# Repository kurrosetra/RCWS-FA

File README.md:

# RCWS-FA
RCWS TA2018 (First Article)

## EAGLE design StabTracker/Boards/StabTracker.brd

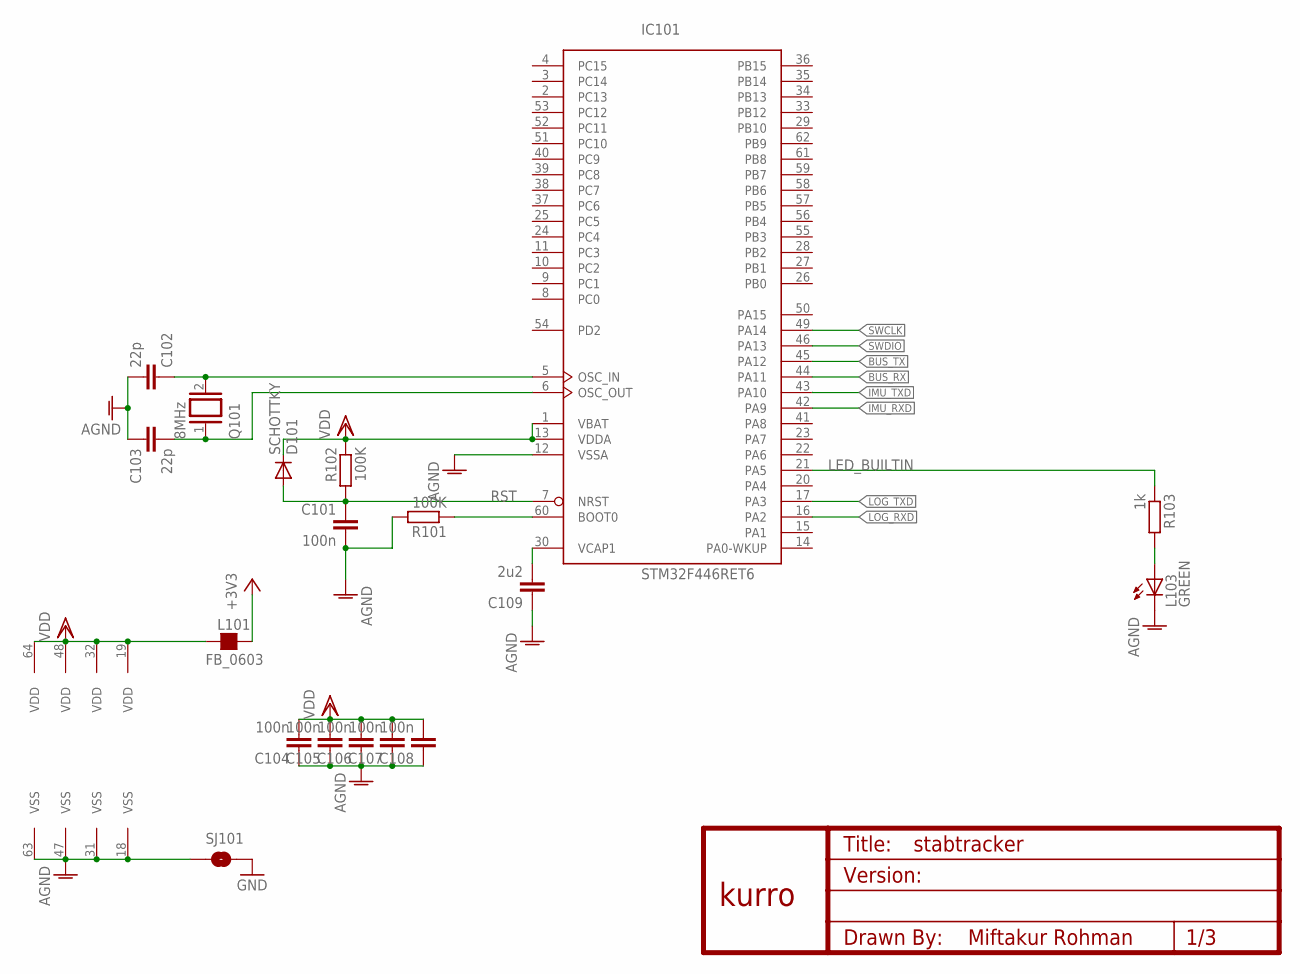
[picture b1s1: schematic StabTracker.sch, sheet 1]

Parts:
C101, C104, C105, C106, C107, C108: 100n; C0603
C102, C103: 22p; C0603
C109: 2u2; C0603
D101: SCHOTTKY; MICROMELF-W
IC101: STM32F446RET6; LQFP64
L101: FB_0603; L0603
L103: GREEN; CHIP-LED0805
Q101: 8MHz; QS
R101, R102: 100K; R0603
R103: 1k; R0603
SJ101: SOLDERJUMPERTRACE; SJ_2S-TRACE
U$1: KURRO_FOOTPRINT; KURRO-LOGO

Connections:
+3V3: L101.2; also elsewhere on the board
AGND: C101.2, C102.2, C103.1, C104.1, C105.1, C106.1, C107.1, C108.1, C109.1, IC101.12 (VSSA), IC101.18 (VSS), IC101.31 (VSS), IC101.47 (VSS), IC101.63 (VSS), L103.C, R101.2, SJ101.1; also elsewhere on the board
BOOT0: IC101.60 (BOOT0), R101.1
BUS_RX: IC101.44 (PA11); also elsewhere on the board
BUS_TX: IC101.45 (PA12); also elsewhere on the board
GND: SJ101.2; also elsewhere on the board
IMU_RXD: IC101.42 (PA9); also elsewhere on the board
IMU_TXD: IC101.43 (PA10); also elsewhere on the board
LED_BUILTIN: IC101.21 (PA5), R103.1
LOG_RXD: IC101.16 (PA2); also elsewhere on the board
LOG_TXD: IC101.17 (PA3); also elsewhere on the board
unnamed: C103.2, IC101.6 (OSC_OUT), Q101.1
unnamed: C102.1, IC101.5 (OSC_IN), Q101.2
unnamed: C109.2, IC101.30 (VCAP1)
unnamed: L103.A, R103.2
RST: C101.1, D101.A, IC101.7 (NRST), R102.2
SWCLK: IC101.49 (PA14); also elsewhere on the board
SWDIO: IC101.46 (PA13); also elsewhere on the board
VDD: C104.2, C105.2, C106.2, C107.2, C108.2, D101.C, IC101.1 (VBAT), IC101.13 (VDDA), IC101.19 (VDD), IC101.32 (VDD), IC101.48 (VDD), IC101.64 (VDD), L101.1, R102.1

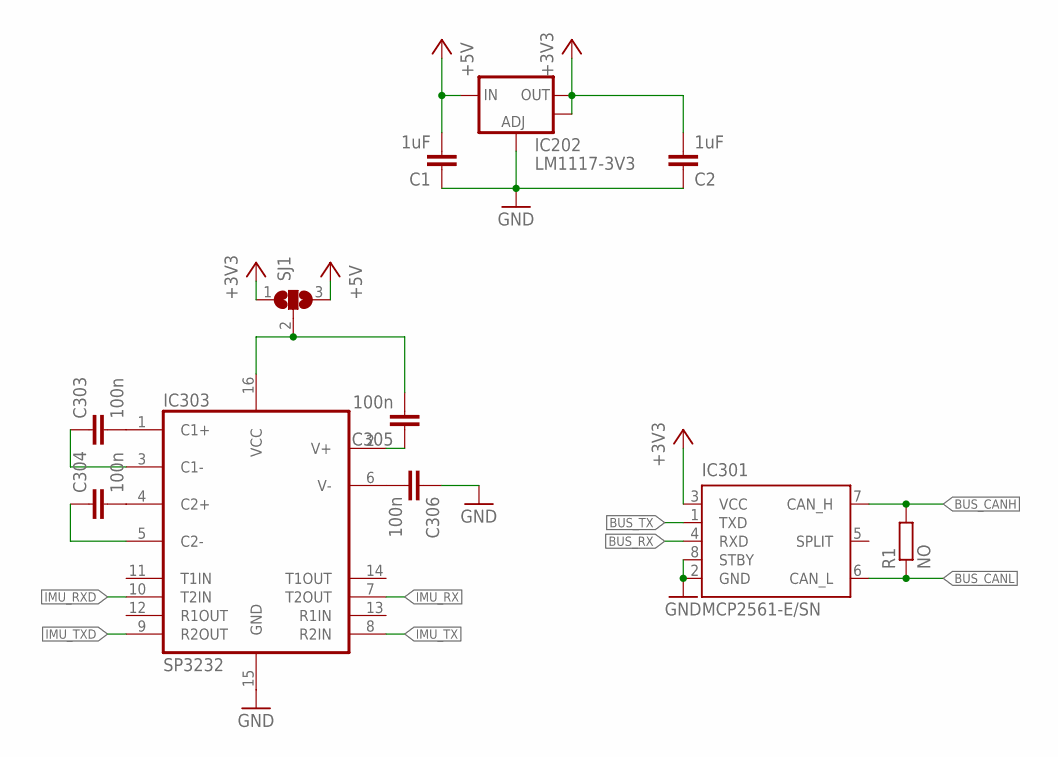
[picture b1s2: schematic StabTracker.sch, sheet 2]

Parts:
C1, C2: 1uF; C0603
C303, C304, C305, C306: 100n; C0603
IC202: LM1117-3V3; SOT223
IC301: MCP2561-E/SN; SOIC-8
IC303: SP3232; SO016
R1: NO; R0603
SJ1: SJ2W-TRACE; SJ2

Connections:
+3V3: C2.2, IC202.2 (OUT), IC202.4 (OUT), IC301.3 (VCC), SJ1.1; also elsewhere on the board
+5V: C1.2, IC202.3 (IN), SJ1.3; also elsewhere on the board
BUS_CANH: IC301.7 (CAN_H), R1.2; also elsewhere on the board
BUS_CANL: IC301.6 (CAN_L), R1.1; also elsewhere on the board
BUS_RX: IC301.4 (RXD); also elsewhere on the board
BUS_TX: IC301.1 (TXD); also elsewhere on the board
GND: C1.1, C2.1, C306.1, IC202.1 (ADJ), IC301.2 (GND), IC301.8 (STBY), IC303.15 (GND); also elsewhere on the board
IMU_RX: IC303.7 (T2OUT); also elsewhere on the board
IMU_RXD: IC303.10 (T2IN); also elsewhere on the board
IMU_TX: IC303.8 (R2IN); also elsewhere on the board
IMU_TXD: IC303.9 (R2OUT); also elsewhere on the board
unnamed: C305.2, IC303.16 (VCC), SJ1.2
unnamed: C306.2, IC303.6 (V-)
unnamed: C303.2, IC303.1 (C1+)
unnamed: C304.2, IC303.4 (C2+)
unnamed: C303.1, IC303.3 (C1-)
unnamed: C304.1, IC303.5 (C2-)
unnamed: C305.1, IC303.2 (V+)

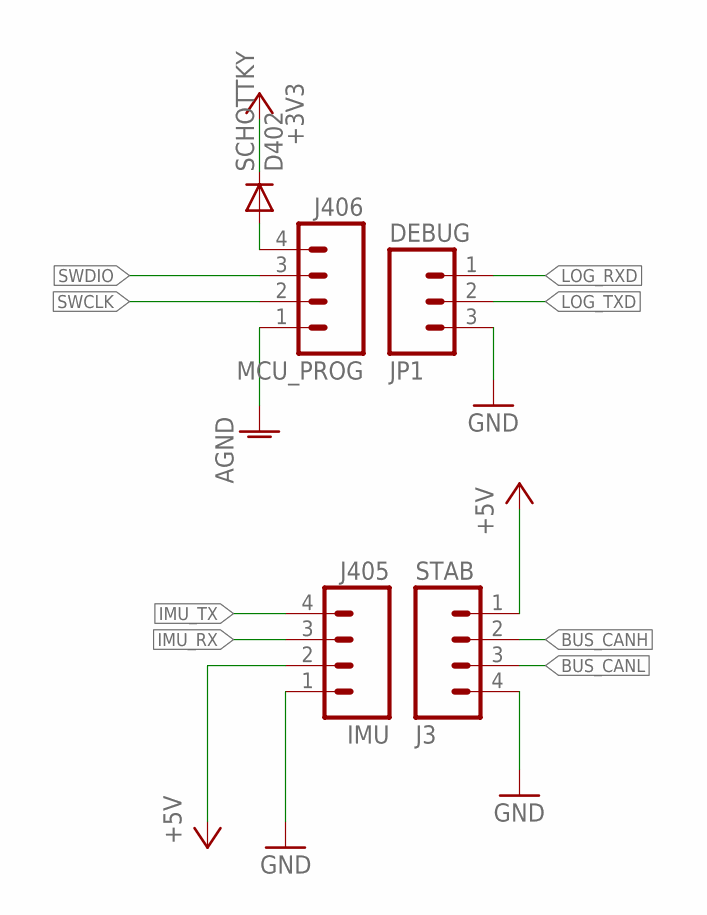
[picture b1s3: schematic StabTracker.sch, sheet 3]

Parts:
D402: SCHOTTKY; MICROMELF-W
J3: STAB; XH-4-RA
J405: IMU; XH-4-RA
J406: MCU_PROG; XH-4-RA
JP1: DEBUG; XH-3-RA

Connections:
+3V3: D402.C; also elsewhere on the board
+5V: J3.1, J405.2; also elsewhere on the board
AGND: J406.1; also elsewhere on the board
BUS_CANH: J3.2; also elsewhere on the board
BUS_CANL: J3.3; also elsewhere on the board
GND: J3.4, J405.1, JP1.3; also elsewhere on the board
IMU_RX: J405.3; also elsewhere on the board
IMU_TX: J405.4; also elsewhere on the board
LOG_RXD: JP1.1; also elsewhere on the board
LOG_TXD: JP1.2; also elsewhere on the board
unnamed: D402.A, J406.4
SWCLK: J406.2; also elsewhere on the board
SWDIO: J406.3; also elsewhere on the board

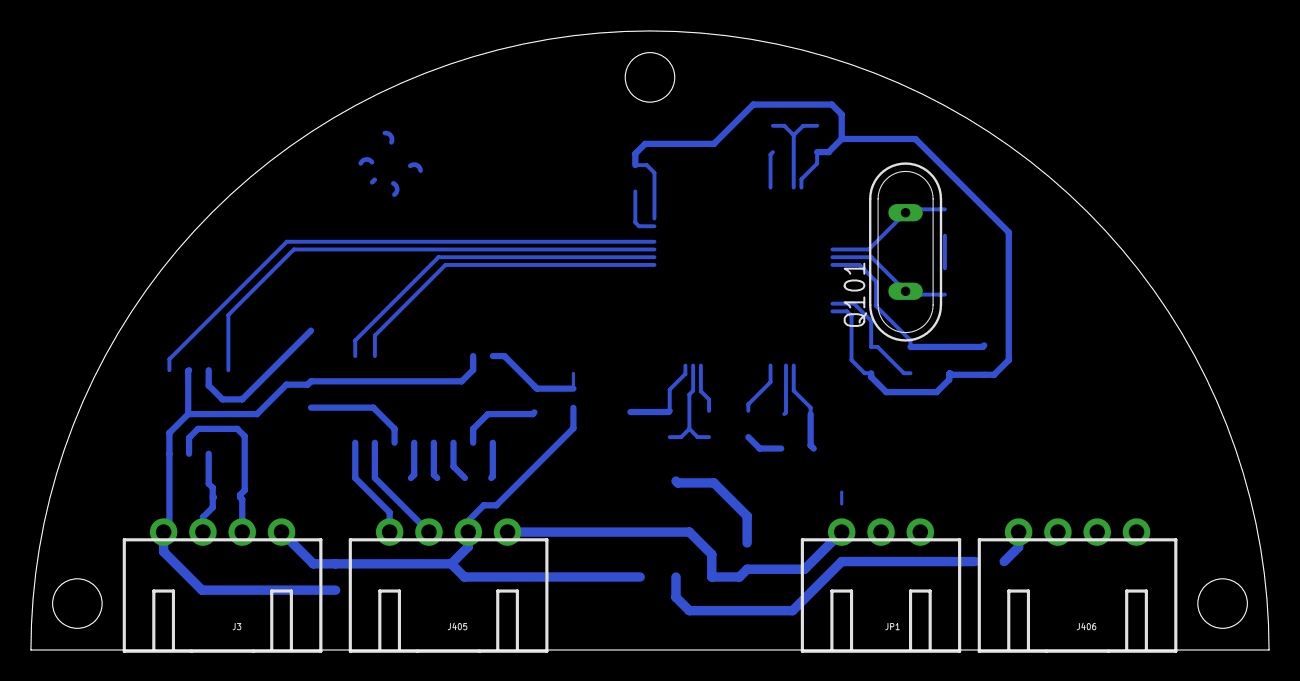
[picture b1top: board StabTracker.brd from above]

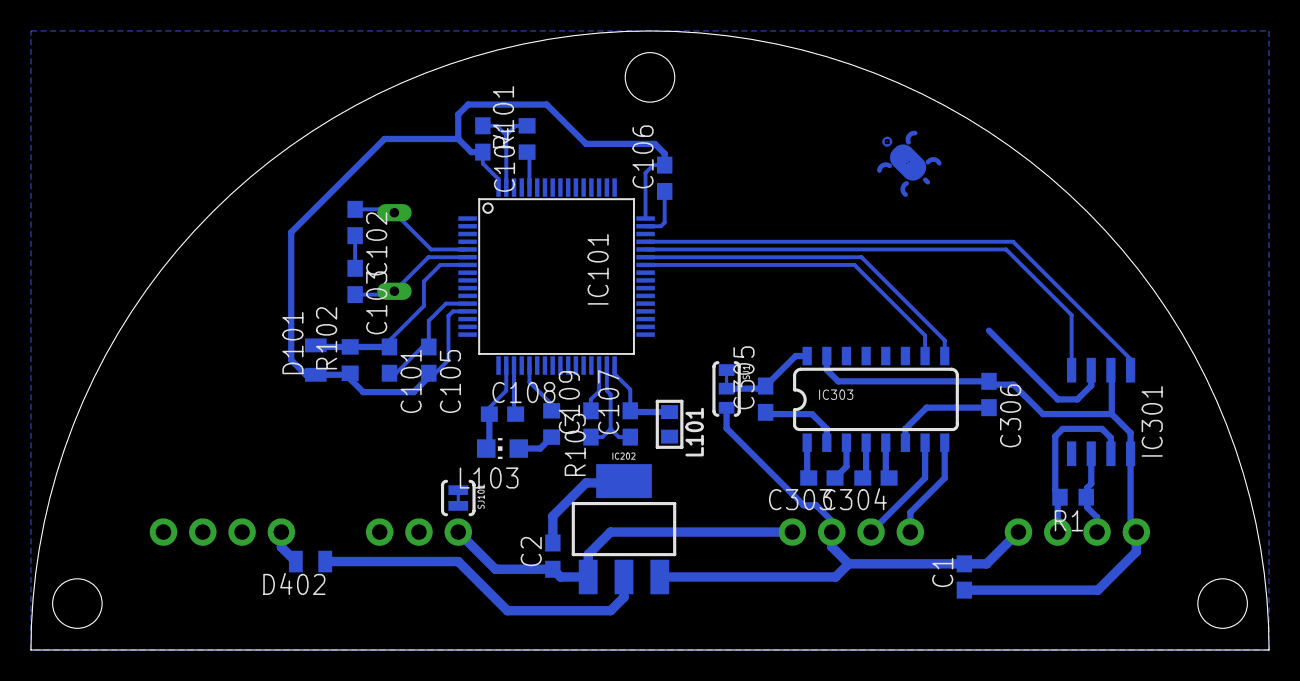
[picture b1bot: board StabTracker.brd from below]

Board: 2 copper layers, 80.0 x 40.0 mm, 35 parts (29 on the bottom side), 32 nets.

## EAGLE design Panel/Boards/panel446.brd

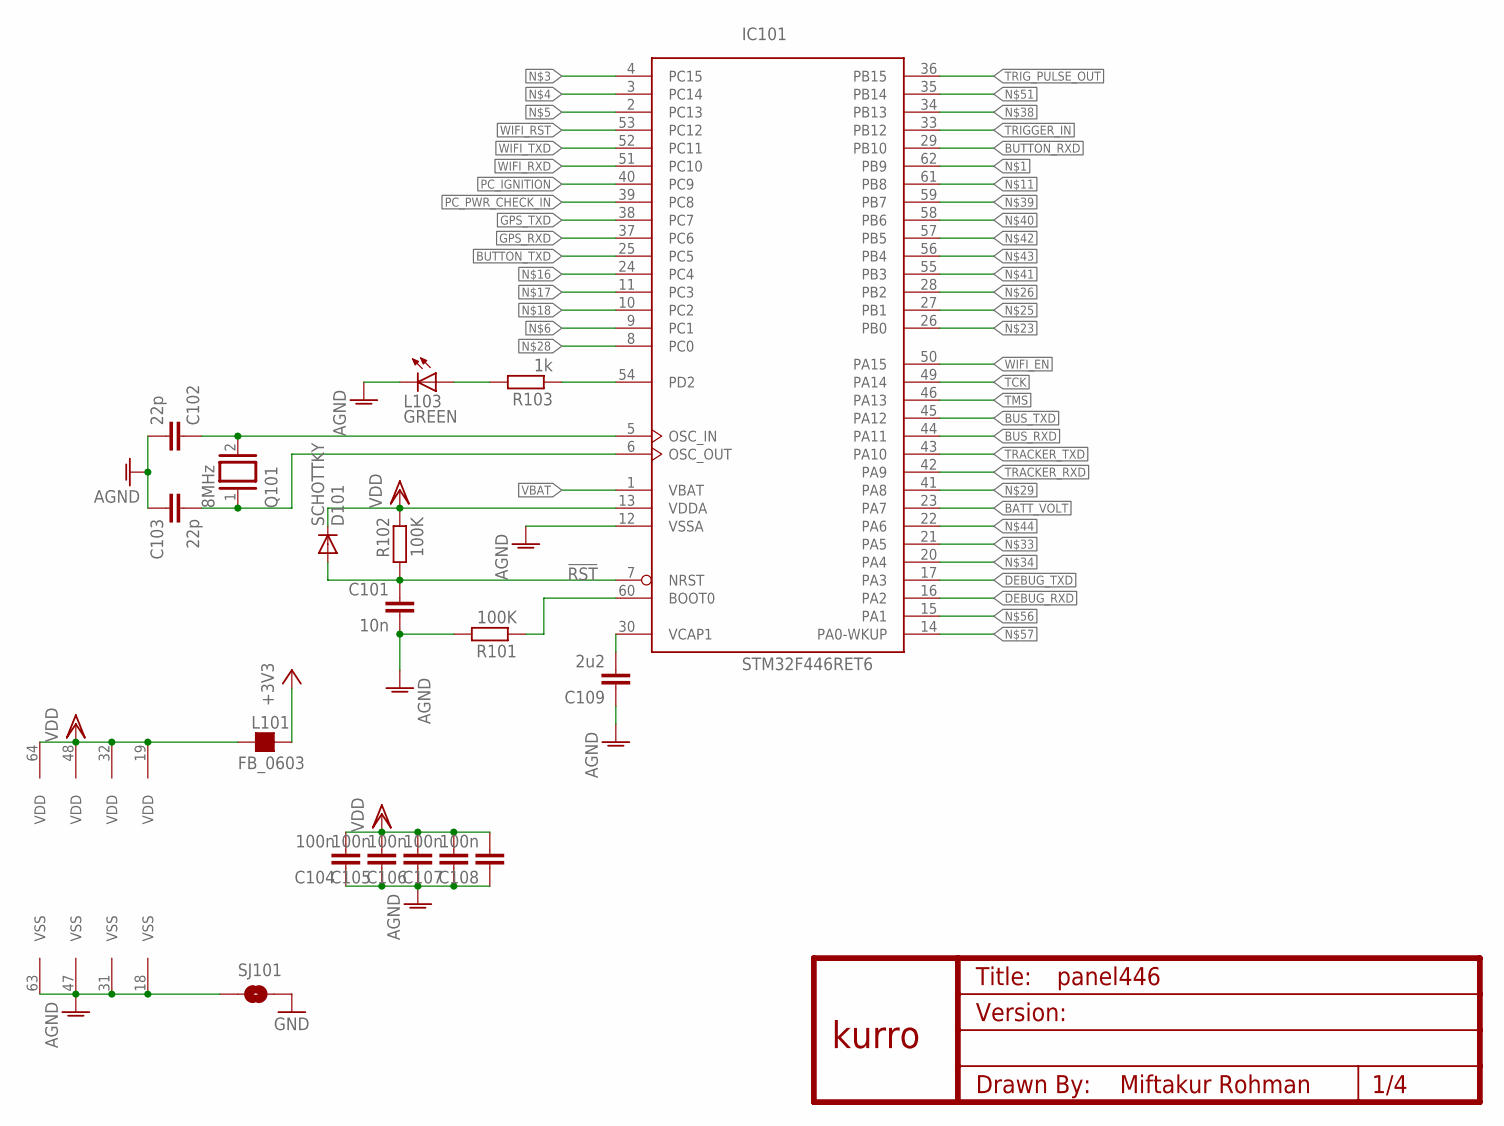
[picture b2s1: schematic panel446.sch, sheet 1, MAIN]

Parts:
C101: 10n; C0603
C102, C103: 22p; C0603
C104, C105, C106, C107, C108: 100n; C0603
C109: 2u2; C0805
D101: SCHOTTKY; MICROMELF-W
IC101: STM32F446RET6; LQFP64
L101: FB_0603; L0603
L103: GREEN; CHIP-LED0805
Q101: 8MHz; QS
R101, R102: 100K; R0603
R103: 1k; R0603
SJ101: SOLDERJUMPERTRACE; SJ_2S-TRACE
U$1: KURRO_FOOTPRINT; KURRO-LOGO

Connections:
!RST: C101.1, D101.A, IC101.7 (NRST), R102.2; also elsewhere on the board
+3V3: L101.2; also elsewhere on the board
AGND: C101.2, C102.2, C103.1, C104.1, C105.1, C106.1, C107.1, C108.1, C109.1, IC101.12 (VSSA), IC101.18 (VSS), IC101.31 (VSS), IC101.47 (VSS), IC101.63 (VSS), L103.C, R101.2, SJ101.1; also elsewhere on the board
BATT_VOLT: IC101.23 (PA7); also elsewhere on the board
BOOT1: IC101.60 (BOOT0), R101.1
BUS_RXD: IC101.44 (PA11); also elsewhere on the board
BUS_TXD: IC101.45 (PA12); also elsewhere on the board
BUTTON_RXD: IC101.29 (PB10); also elsewhere on the board
BUTTON_TXD: IC101.25 (PC5); also elsewhere on the board
DEBUG_RXD: IC101.16 (PA2); also elsewhere on the board
DEBUG_TXD: IC101.17 (PA3); also elsewhere on the board
GND: SJ101.2; also elsewhere on the board
GPS_RXD: IC101.37 (PC6); also elsewhere on the board
GPS_TXD: IC101.38 (PC7); also elsewhere on the board
unnamed: C109.2, IC101.30 (VCAP1)
unnamed: IC101.54 (PD2), R103.1
unnamed: L103.A, R103.2
unnamed: C103.2, IC101.6 (OSC_OUT), Q101.1
unnamed: C102.1, IC101.5 (OSC_IN), Q101.2
PC_IGNITION: IC101.40 (PC9); also elsewhere on the board
PC_PWR_CHECK_IN: IC101.39 (PC8); also elsewhere on the board
TCK: IC101.49 (PA14); also elsewhere on the board
TMS: IC101.46 (PA13); also elsewhere on the board
TRACKER_RXD: IC101.42 (PA9); also elsewhere on the board
TRACKER_TXD: IC101.43 (PA10); also elsewhere on the board
TRIGGER_IN: IC101.33 (PB12); also elsewhere on the board
TRIG_PULSE_OUT: IC101.36 (PB15); also elsewhere on the board
VBAT: IC101.1 (VBAT)
VDD: C104.2, C105.2, C106.2, C107.2, C108.2, D101.C, IC101.13 (VDDA), IC101.19 (VDD), IC101.32 (VDD), IC101.48 (VDD), IC101.64 (VDD), L101.1, R102.1; also elsewhere on the board
WIFI_EN: IC101.50 (PA15); also elsewhere on the board
WIFI_RST: IC101.53 (PC12); also elsewhere on the board
WIFI_RXD: IC101.51 (PC10); also elsewhere on the board
WIFI_TXD: IC101.52 (PC11); also elsewhere on the board

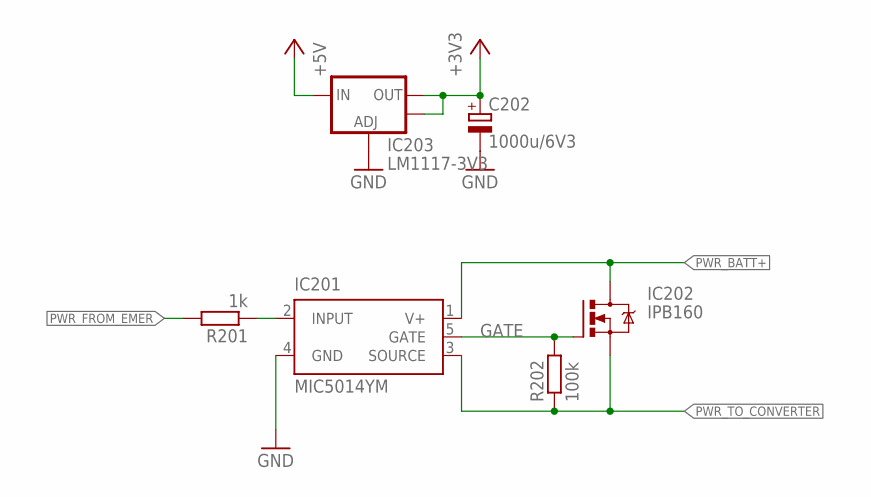
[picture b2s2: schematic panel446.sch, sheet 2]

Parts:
C202: 1000u/6V3; 153CLV-0810
IC201: MIC5014YM; SO-08
IC202: IPB160; PG-TO263-7
IC203: LM1117-3V3; SOT223
R201: 1k; R0603
R202: 100k; R0603

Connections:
+3V3: C202.+, IC203.2 (OUT), IC203.4 (OUT); also elsewhere on the board
+5V: IC203.3 (IN); also elsewhere on the board
GATE: IC201.5 (GATE), IC202.1 (G), R202.2
GND: C202.-, IC201.4 (GND), IC203.1 (ADJ); also elsewhere on the board
unnamed: IC201.2 (INPUT), R201.1
PWR_BATT+: IC201.1 (V+), IC202.4 (D); also elsewhere on the board
PWR_FROM_EMER: R201.2; also elsewhere on the board
PWR_TO_CONVERTER: IC201.3 (SOURCE), IC202.2 (S), IC202.3 (S), IC202.5 (S), IC202.6 (S), IC202.7 (S), R202.1; also elsewhere on the board

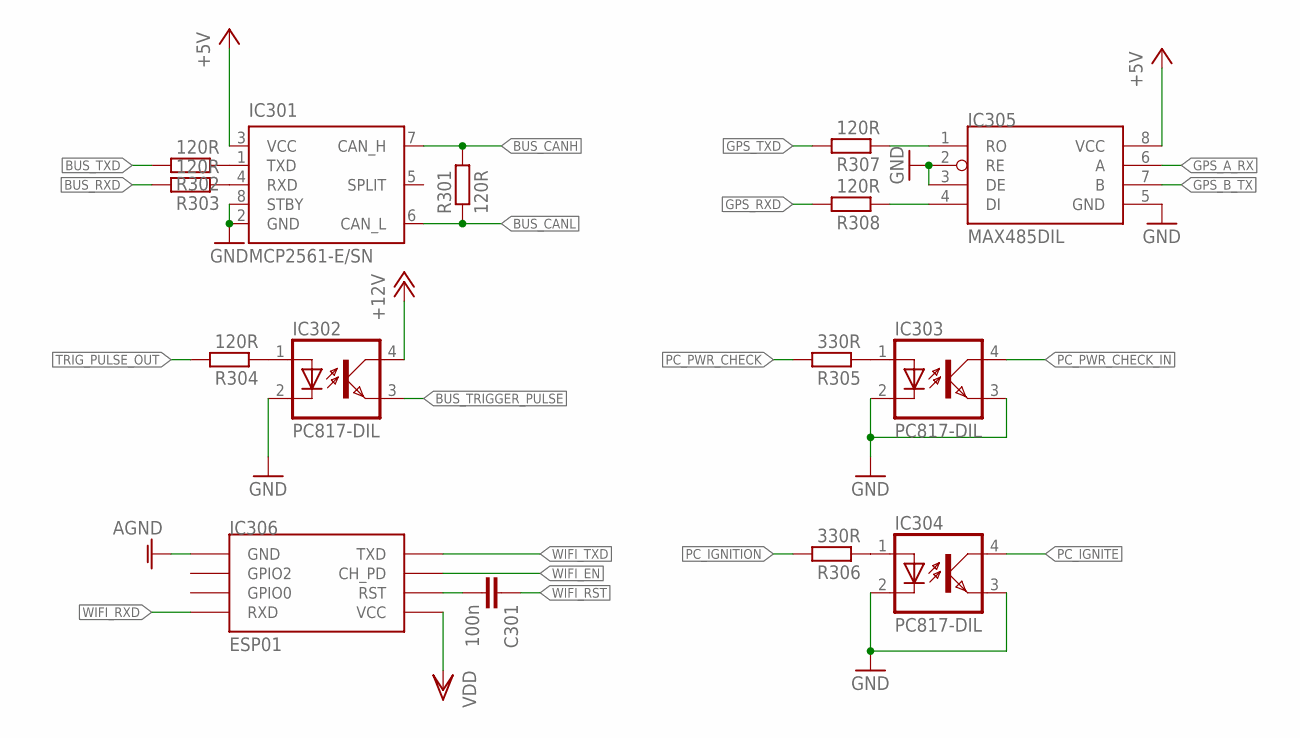
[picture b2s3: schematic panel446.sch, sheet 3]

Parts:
C301: 100n; C0603
IC301: MCP2561-E/SN; SOIC-8
IC302, IC303, IC304: PC817-DIL; DIL04A
IC305: MAX485DIL; DIL08
IC306: ESP01
R301, R302, R303, R304, R307, R308: 120R; R0603
R305, R306: 330R; R0603

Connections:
+5V: IC301.3 (VCC), IC305.8 (VCC); also elsewhere on the board
+12V: IC302.4 (COL); also elsewhere on the board
AGND: IC306.GND; also elsewhere on the board
BUS_CANH: IC301.7 (CAN_H), R301.2; also elsewhere on the board
BUS_CANL: IC301.6 (CAN_L), R301.1; also elsewhere on the board
BUS_RXD: R303.2; also elsewhere on the board
BUS_TRIGGER_PULSE: IC302.3 (EMIT); also elsewhere on the board
BUS_TXD: R302.2; also elsewhere on the board
GND: IC301.2 (GND), IC301.8 (STBY), IC302.2 (C), IC303.2 (C), IC303.3 (EMIT), IC304.2 (C), IC304.3 (EMIT), IC305.2 (RE), IC305.3 (DE), IC305.5 (GND); also elsewhere on the board
GPS_A_RX: IC305.6 (A); also elsewhere on the board
GPS_B_TX: IC305.7 (B); also elsewhere on the board
GPS_RXD: R308.2; also elsewhere on the board
GPS_TXD: R307.2; also elsewhere on the board
unnamed: C301.2, IC306.RST
unnamed: IC301.4 (RXD), R303.1
unnamed: IC301.1 (TXD), R302.1
unnamed: IC302.1 (A), R304.1
unnamed: IC303.1 (A), R305.1
unnamed: IC305.1 (RO), R307.1
unnamed: IC305.4 (DI), R308.1
unnamed: IC304.1 (A), R306.1
PC_IGNITE: IC304.4 (COL); also elsewhere on the board
PC_IGNITION: R306.2; also elsewhere on the board
PC_PWR_CHECK: R305.2; also elsewhere on the board
PC_PWR_CHECK_IN: IC303.4 (COL); also elsewhere on the board
TRIG_PULSE_OUT: R304.2; also elsewhere on the board
VDD: IC306.VCC; also elsewhere on the board
WIFI_EN: IC306.CH_PD; also elsewhere on the board
WIFI_RST: C301.1; also elsewhere on the board
WIFI_RXD: IC306.RX (RXD); also elsewhere on the board
WIFI_TXD: IC306.TX (TXD); also elsewhere on the board

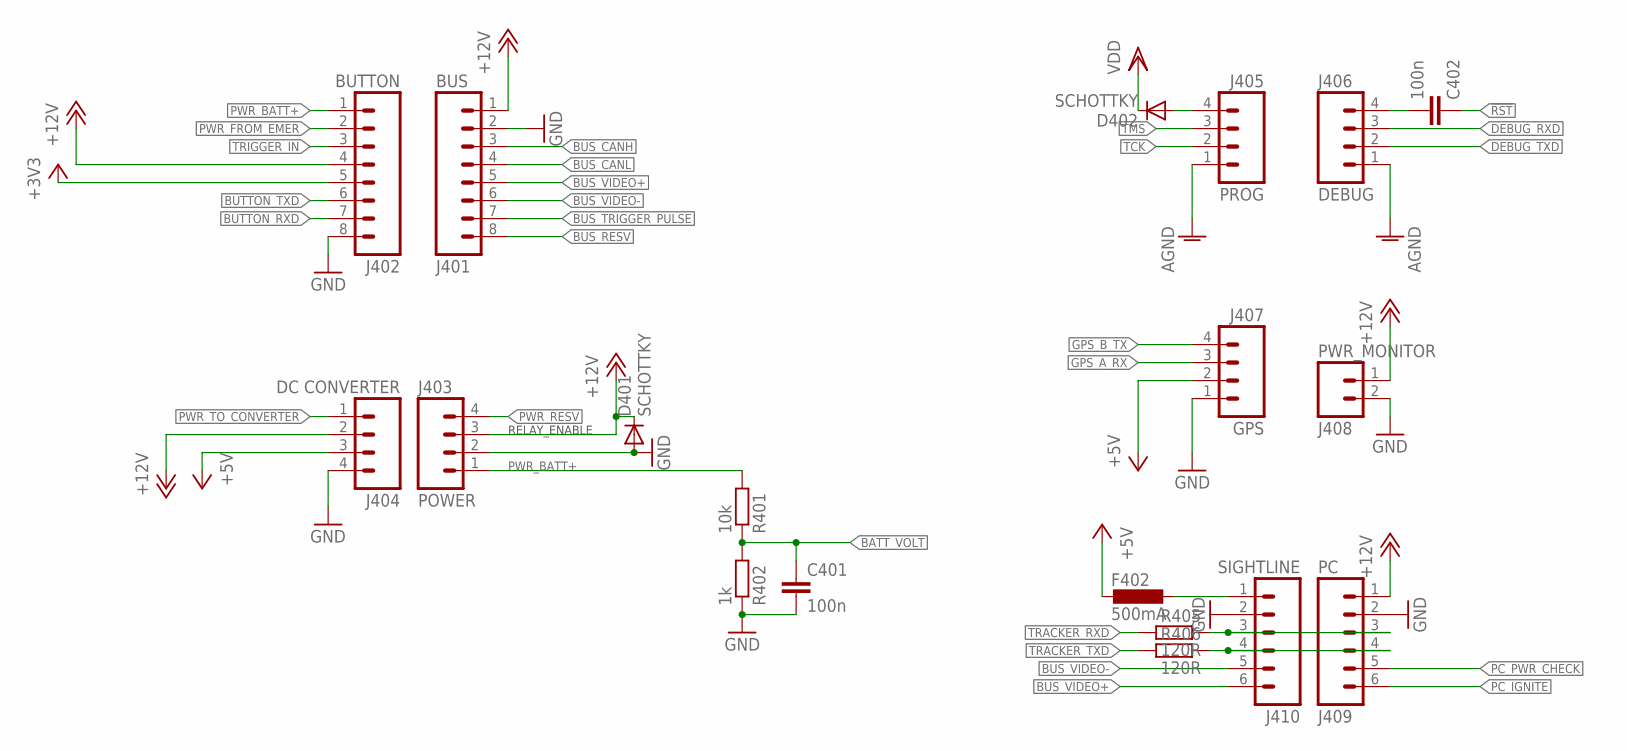
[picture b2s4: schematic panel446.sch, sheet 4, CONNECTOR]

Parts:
C401, C402: 100n; C0603
D401, D402: SCHOTTKY; MICROMELF-W
F402: 500mA; L0805
J401: BUS; XH-8-VERT
J402: BUTTON; XH-8-VERT
J403: POWER; XH-4-VERT
J404: DC CONVERTER; XH-4-VERT
J405: PROG; XH-4-VERT
J406: DEBUG; XH-4-VERT
J407: GPS; XH-4-VERT
J408: PWR_MONITOR; XH-2-RA
J409: PC; XH-6-VERT
J410: SIGHTLINE; XH-6-VERT
R401: 10k; R0603
R402: 1k; R0603
R405, R406: 120R; R0603

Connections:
!RST: C402.1; also elsewhere on the board
+3V3: J402.5; also elsewhere on the board
+5V: F402.2, J404.3, J407.2; also elsewhere on the board
+12V: D401.C, J401.1, J402.4, J403.3, J404.2, J408.1, J409.1; also elsewhere on the board
AGND: J405.1, J406.1; also elsewhere on the board
BATT_VOLT: C401.1, R401.1, R402.2; also elsewhere on the board
BUS_CANH: J401.3; also elsewhere on the board
BUS_CANL: J401.4; also elsewhere on the board
BUS_RESV: J401.8
BUS_TRIGGER_PULSE: J401.7; also elsewhere on the board
BUS_VIDEO+: J401.5, J410.6
BUS_VIDEO-: J401.6, J410.5
BUTTON_RXD: J402.7; also elsewhere on the board
BUTTON_TXD: J402.6; also elsewhere on the board
DEBUG_RXD: J406.3; also elsewhere on the board
DEBUG_TXD: J406.2; also elsewhere on the board
GND: C401.2, D401.A, J401.2, J402.8, J403.2, J404.4, J407.1, J408.2, J409.2, J410.2, R402.1; also elsewhere on the board
GPS_A_RX: J407.3; also elsewhere on the board
GPS_B_TX: J407.4; also elsewhere on the board
unnamed: J409.3, J410.3, R405.1
unnamed: J409.4, J410.4, R406.1
unnamed: D402.A, J405.4
unnamed: C402.2, J406.4
unnamed: F402.1, J410.1
PC_IGNITE: J409.6; also elsewhere on the board
PC_PWR_CHECK: J409.5; also elsewhere on the board
PWR_BATT+: J402.1, J403.1, R401.2; also elsewhere on the board
PWR_FROM_EMER: J402.2; also elsewhere on the board
PWR_RESV: J403.4
PWR_TO_CONVERTER: J404.1; also elsewhere on the board
TCK: J405.2; also elsewhere on the board
TMS: J405.3; also elsewhere on the board
TRACKER_RXD: R405.2; also elsewhere on the board
TRACKER_TXD: R406.2; also elsewhere on the board
TRIGGER_IN: J402.3; also elsewhere on the board
VDD: D402.C; also elsewhere on the board

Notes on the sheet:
RELAY_ENABLE

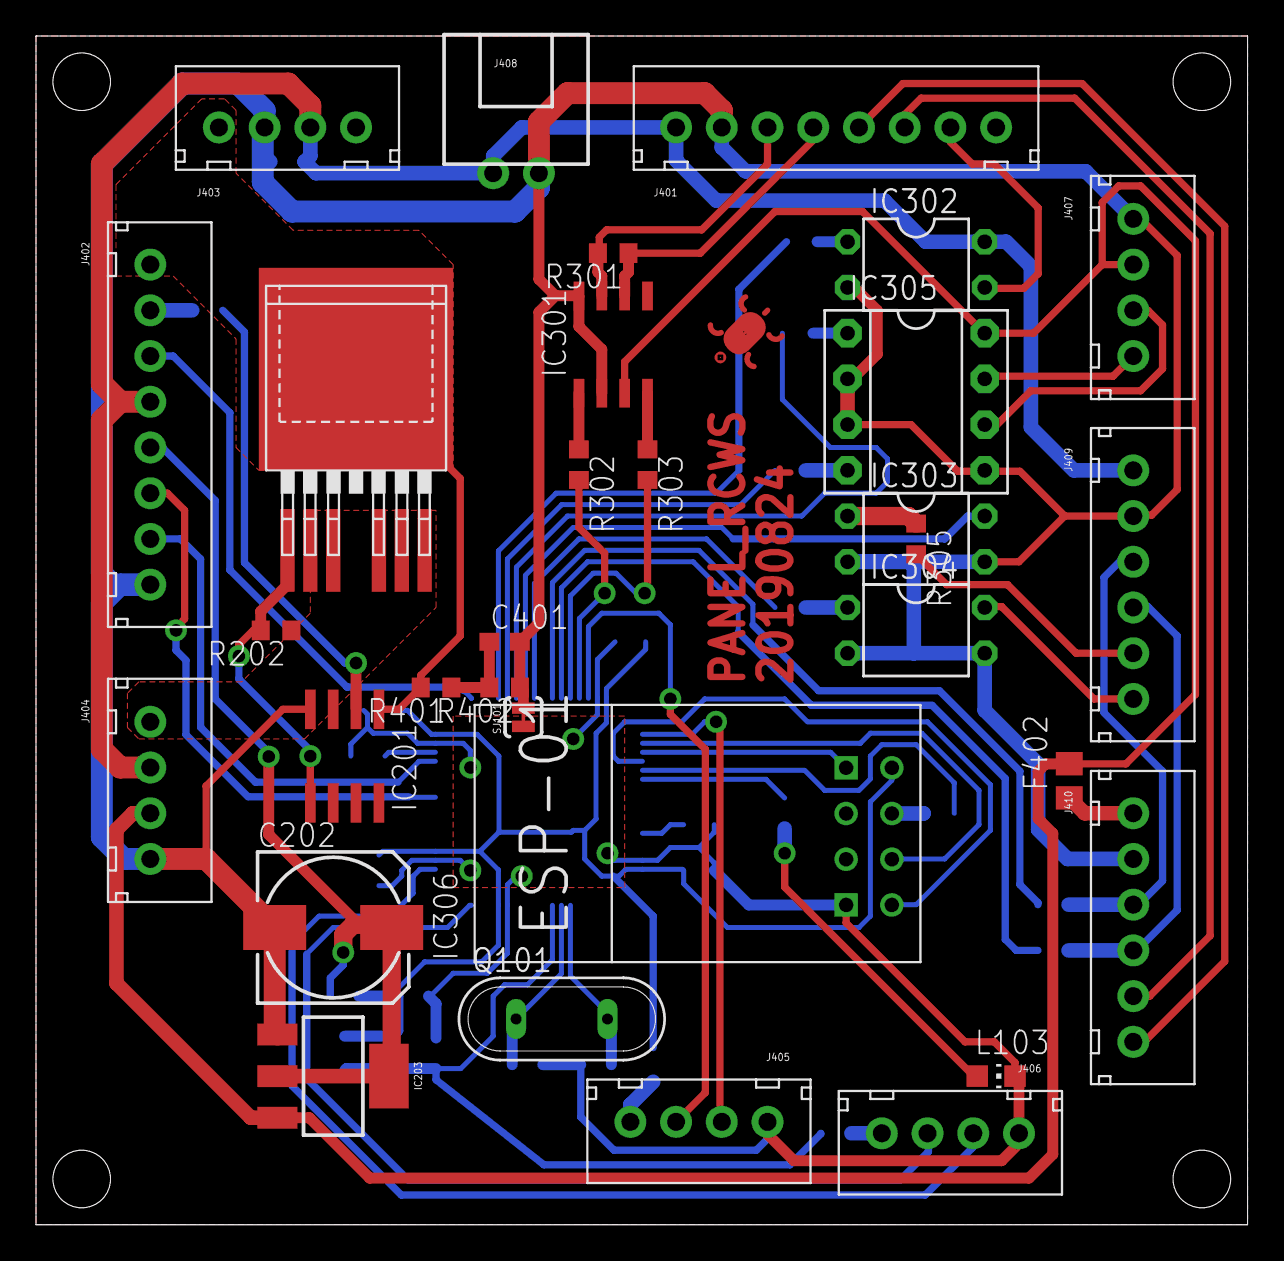
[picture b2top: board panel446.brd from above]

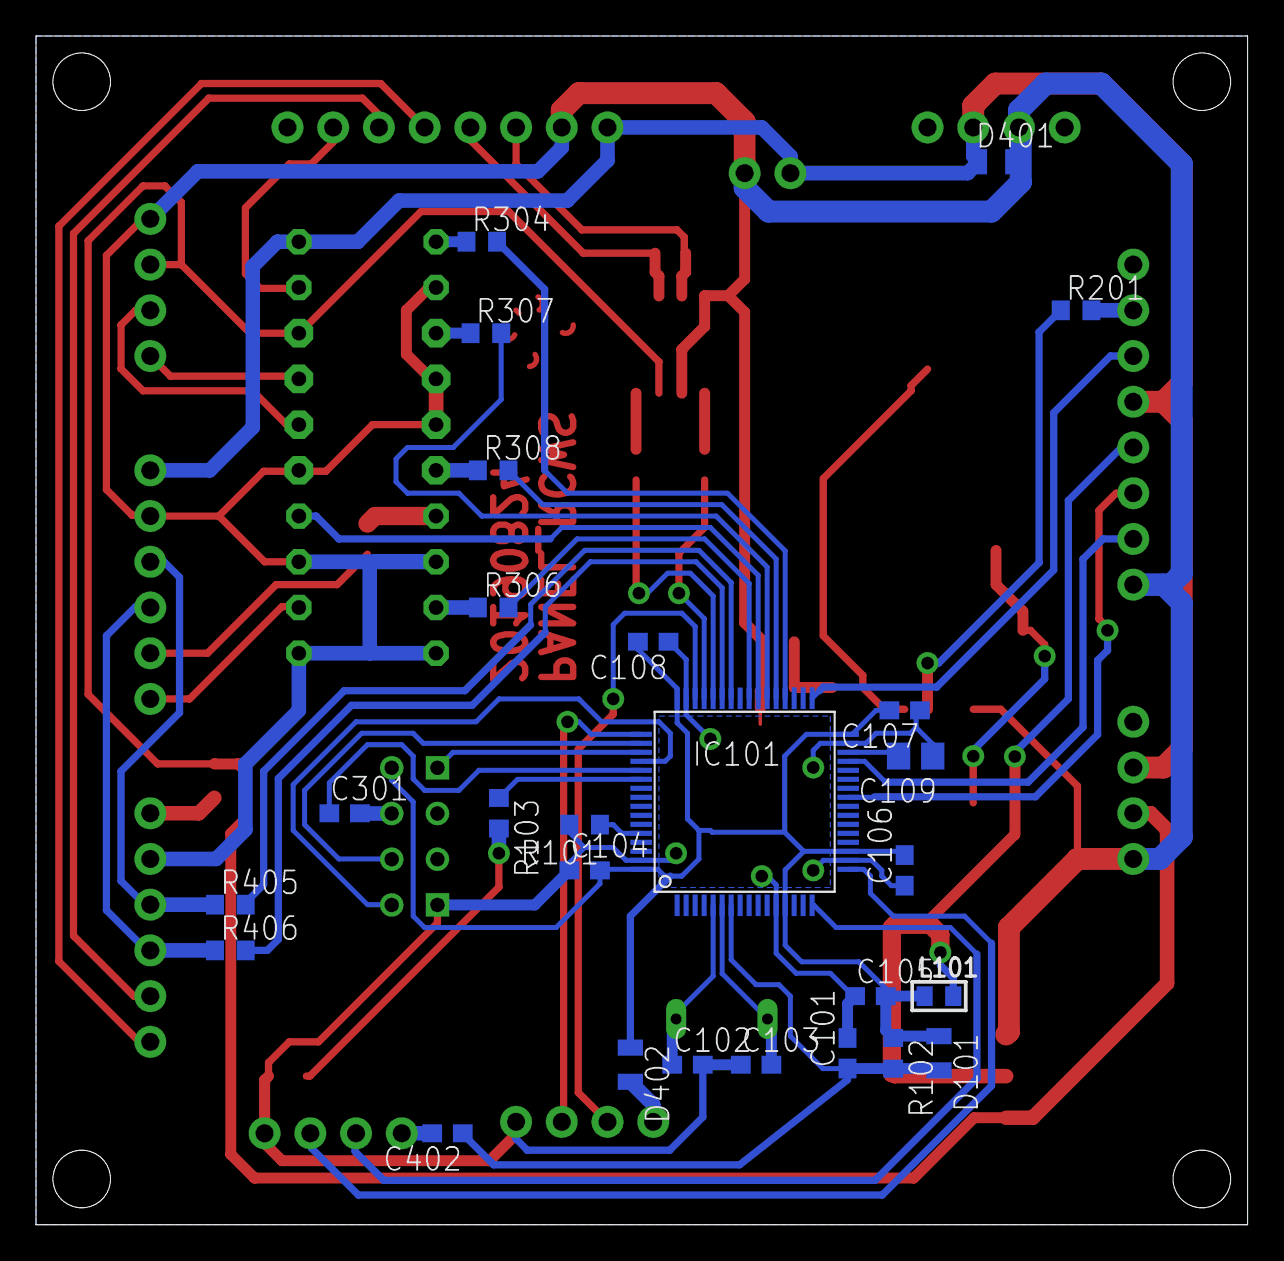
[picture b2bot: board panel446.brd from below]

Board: 2 copper layers, 67.3 x 66.0 mm, 59 parts (27 on the bottom side), 61 nets.

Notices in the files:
MotorControl/Firmwares/motorController/Src/main.c:
© Copyright (c) 2020 STMicroelectronics.
All rights reserved.
This software component is licensed by ST under BSD 3-Clause license,
the "License"; You may not use this file except in compliance with the
License. You may obtain a copy of the License at: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
(C) COPYRIGHT STMicroelectronics *****END OF FILE
Panel/Firmwares/panel_F446/Src/main_20191023.c:
COPYRIGHT(c) 2019 STMicroelectronics
parts and their libraries:
rc-master: Copyright (C) 2007, Bob Starr
